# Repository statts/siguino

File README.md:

# Siguino

Low power board based on Arduino Pro Mini with in-built Sigfox network support

Siguino Eagle schematics, libraries and Arduino code created by Scott Tattersall

Further project info and manufactured boards for purchase at https://siguino.com

Detailed Getting Started Guide: https://siguino.com/step-by-step-guide/

3rd Party libraries / resources used:

Hardware:
- Many basic components (resistors, capacitors, etc) are from the SparkFun Eagle libraries
- LIS3DH accelerometer from SparkFun: https://github.com/sparkfun/SparkFun_LIS3DH_Arduino_Library
- Wisol Chip from hellogitty/WiSol (greatech.de) https://github.com/hellogitty/WiSOL

Software:
 (To install, go to url and "download zip", in Arduino IDE click Sketch->Include Library->Add zip and select downloaded zip file)
- LowPower library from RocketScream: https://github.com/rocketscream/Low-Power
- SparkFun LIS3DH library (https://github.com/sparkfun/SparkFun_LIS3DH_Arduino_Library)
- Arduino Sensors library (https://github.com/adafruit/Adafruit_Sensor)
- Arduino Bosch BME280 library (https://github.com/adafruit/Adafruit_BME280_Library)
- AltSoftSerial (https://github.com/PaulStoffregen/AltSoftSerial)

Enclosure:
- CAD (STL) files for sample enclosure that can be 3d printed as needed

# Sample projects
Along with the sigfox_sensors project that sends all sensor information here is another simple example project:

- Weather Station (arduino/weather_station)
Follow the same above software section to install the approriate libraries first, then download the weather station code.
The code can be flashed onto the Siguino via a standard FTDI breakout board (3.3v version only!), e.g. 
https://www.sparkfun.com/products/9873

The code: A simple weather station that sends avg temperature, light level, humidity and atmospheric pressure. If using Wia to process the data (see above getting started link), these can be easily graphed in Wia using a Wia Widget:
https://developers.wia.io/docs/add-a-widget

More information on integrating with Wia:
https://siguino.com/getting-started-with-siguino-and-wia-io/

Example:

")

# Eagle libraries
In eagle, set the directories for libraries to add the libary files included here if not already included, e.g.
$EAGLEDIR/lbr:{PROJECT-DIR}/Libraries/SparkFun-Eagle-Libraries-master:{PROJECT-DIR}/Libraries/WiSOL-master/Eagle_Library

Plus use the New Library -> execute script to add the components in script form from the scripts dir

# Hardware Revision History:

Rev 0.1: First version, trimmed board

Rev 0.2:
1) Add Reset Pin out as well as dtr for bootloading
2) Change C8 10uf format to standard 0603
3) Update routing to account for unsaved work
4) Re-write/tidy arduino sketch
5) Add de-coupling caps 10uf, 100nf to Accel chip VDD
6) Connect INT1 pin on Accel to D3

Rev 0.3:
1) Add Battery Holder
2) Add Reverse polarity Protection
3) Reposition Antenna

Rev 0.4:
1) Replace Temperature chip
2) Re-route temperature chip
3) Add registration hole for battery holder
4) Minor re-routing of vias under chips

Rev 0.5 / 1.0:
1) Added Magnetometer
2) Replaced temp chip with Temp & Pressure (Bosch BME 280)
3) Re-routing for manufacturing

Rev 1.1:
1) Improved Schematic (with thanks to Marnix Janse)
2) Improved Antenna trace (with thanks to Marnix Janse)

# Licence & Contact

Siguino Hardware and Software licenced under GPLv3, any questions or issues please contact scott@dock.ie

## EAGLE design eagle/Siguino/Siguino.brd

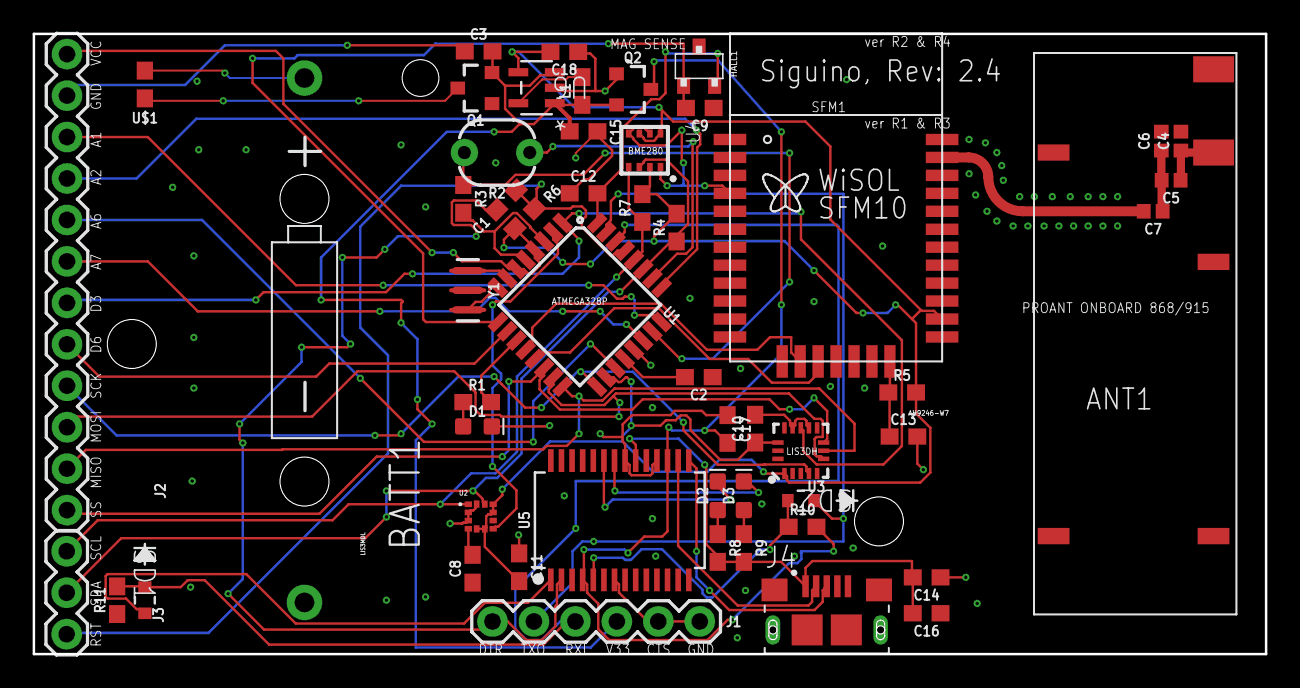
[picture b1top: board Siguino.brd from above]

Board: 2 copper layers, 75.5 x 38.0 mm, 53 parts (0 on the bottom side), 49 nets.

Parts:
ANT1: PRO-OB-471; ONBOARD_SMD_2400
BATT1: SPARKFUN-BATTERIES_CR2-BATTERY-HOLDERPTH; SPARKFUN-BATTERIES_BATTERYHOLDER-CR2
C1, C2, C3, C10, C11, C13, C14, C17: 0.1uF; 0603
C4: 0.6pF; 0402
C5: 2.2pF; 0402
C6: 0.7pF; 0402
C7: 0 OHM; 0402
C8: 100nF; 0603
C9: 10nF; 0603
C12: 100pF; 0603
C15, C16, C18: 10uF; 0603
D1, D2: RED; LED-0603
D3: GREEN; LED-0603
HALL1: TR-J_AH9246-W7; TR-J_SC-59
J1: FTDI; 1X06
J2: 1X12
J3: 1X03
J4: 10118193-0001LF; FCI_10118193-0001LF
L1: 10uH; 0603
Q1, Q2: MOSFET P-CH 20V 5.3A SOT-23; SOT23-3
R1: 330; 0603
R2: PHOTOCELLPTH; PHOTOCELL
R3, R8, R9, R10, R11: 1k; 0603
R4, R6, R7: 10k; 0603
R5: 100k; 0603
SD1, SD2: SD0603
SFM1: WISOL_WSSFM10
U1: ATMEGA328P_TQFP; TQFP32-08
U2: LIS3MDLTR_LIS3MDLTR; LIS3MDLTR_LGA12R50P4X4_200X200X100
U3: SPARKFUN-SENSORS_LIS3DH; SPARKFUN-SENSORS_LGA-16-3X3
U4: BME280; BME280COMPONENTLIBRARY_BME280_LGA
U5: FT232RL; SSOP28DB
U6: MAX1724EZK33+T; 21-0113C
U$1: PPTC; 0603
Y1: 8MHz; RESONATOR-SMD-3.2X1.3

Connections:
3V3FTDI: C17.2, Q2.3, R10.2, U5.4, U5.17
5V: C14.2, C16.2, J4.1, R8.2, R9.2, U5.20
A1: J2.10, U1.24
A2: J2.9, U1.25
A6: J2.8, U1.19
A7: J2.7, U1.22
D6: J2.5, U1.10
D7: R1.2, U1.11
DTR: C1.1, J1.1, U5.2
GND: ANT1.GND, BATT1.GND, C2.1, C3.1, C4.2, C6.2, C8.1, C9.1, C10.2, C11.1, C12.1, C13.2, C14.1, C15.1, C16.1, C17.1, C18.1, D1.C, HALL1.3, J1.5, J1.6, J2.11, J4.5, J4.S1, J4.S2, J4.S3, J4.S4, J4.S5, J4.S6, Q1.1, Q2.1, R3.2, R11.1, SFM1.1, SFM1.2, SFM1.3, SFM1.4, SFM1.20, SFM1.22, SFM1.27, SFM1.28, SFM1.29, SFM1.31, U1.3, U1.5, U1.21, U2.2, U2.3, U2.12, U3.5, U3.10, U3.12, U4.P$1, U4.P$5, U4.P$7, U5.7, U5.11, U5.18, U5.21, U5.25, U5.26, U6.2, Y1.2
HALL_POWER: C9.2, HALL1.1, U1.9
HALL_SENSE: C12.2, HALL1.2, U1.32
INT1: J2.6, U1.1, U3.11
LIGHT_POWER: R2.1, U1.26
LIGHT_SENSE: R2.2, R3.1, U1.23
MAG_INT: U1.2, U2.7
MISO: J2.2, U1.16, U3.7
MOSI: J2.3, U1.15, U3.6
unnamed: C2.2, U1.20
unnamed: U1.8, Y1.3
unnamed: U1.7, Y1.1
unnamed: ANT1.RF_FEED, C4.1, C5.1
unnamed: C13.1, R5.1, SFM1.19
unnamed: SD1.2, U5.1
unnamed: C5.2, C6.1, C7.1
unnamed: C8.2, U2.4
unnamed: R10.1, SD2.2, U5.5
unnamed: D2.A, R8.1
unnamed: D3.A, R9.1
unnamed: D2.C, U5.23
unnamed: D3.C, U5.22
unnamed: J4.2, U5.16
unnamed: J4.3, U5.15
unnamed: L1.2, U6.5
unnamed: D1.A, R1.1
RESET: C1.2, J3.1, R6.1, U1.29
RXI: J1.3, R11.2, SD1.1, U1.30
SCK: J2.4, U1.17, U3.4
SCL: J3.3, R7.1, U1.28, U2.1, U4.P$4
SDA: J3.2, R4.1, U1.27, U2.11, U4.P$3
SIG_RX: SFM1.15, U1.13
SIG_TX: SFM1.14, U1.12
SS: J2.1, U1.14, U3.8
TXO: J1.2, SD2.1, U1.31
VBAT: BATT1.VBATT, U$1.1
VBAT2: C3.2, C15.2, J1.4, L1.1, Q1.2, Q2.2, U6.1, U6.3
VCC: C10.1, C11.2, C18.2, J2.12, R4.2, R5.2, R6.2, R7.2, SFM1.21, U1.4, U1.6, U1.18, U2.5, U2.6, U2.9, U2.10, U3.1, U3.14, U4.P$2, U4.P$6, U4.P$8, U6.4
VSAFE: Q1.3, U$1.2
WISOL_ANT: C7.2, SFM1.30

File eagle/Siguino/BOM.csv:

"Part";"Value";"Device";"Package";"Description";"DESCRIPTION";"DIGI-KEY_PART_NUMBER";"DIGI-KEY_PURCHASE_URL";"MF";"MP";"PACKAGE";"PROD_ID";"SF_ID";"VALUE";
"ANT1";"PROOB471";"PROANT_PRO-OB-471_ONBOARD";"PROANT_ONBOARD_SMD_868_915";"Proant OnBoard Antenna PRO-OB-471 for 868/915MHz comms (e.g. SigFox)";"";"";"";"";"";"";"";"";"";
"BATT1";"SPARKFUN-BATTERIES_CR2-BATTERY-HOLDERPTH";"SPARKFUN-BATTERIES_CR2-BATTERY-HOLDERPTH";"SPARKFUN-BATTERIES_BATTERYHOLDER-CR2";"CR2 Battery holder from MPD, see DigiKey product here:";"";"";"";"";"";"";"";"";"";
"C1";"0.1uF";"0.1UF-0603-25V-5%";"0603";"0.1µF ceramic capacitors";"";"";"";"";"";"";"CAP-08604";"";"0.1uF";
"C2";"0.1uF";"0.1UF-0603-25V-5%";"0603";"0.1µF ceramic capacitors";"";"";"";"";"";"";"CAP-08604";"";"0.1uF";
"C3";"0.1uF";"0.1UF-0603-25V-5%";"0603";"0.1µF ceramic capacitors";"";"";"";"";"";"";"CAP-08604";"";"0.1uF";
"C4";"0.6pF";"0.8PF-0402-50V-0.1PF";"0402";"0.8pF ceramic capacitors";"";"";"";"";"";"";"CAP-13456";"";"0.8pF";
"C5";"2.2pF";"0.8PF-0402-50V-0.1PF";"0402";"0.8pF ceramic capacitors";"";"";"";"";"";"";"CAP-13456";"";"0.8pF";
"C6";"0.7pF";"0.8PF-0402-50V-0.1PF";"0402";"0.8pF ceramic capacitors";"";"";"";"";"";"";"CAP-13456";"";"0.8pF";
"C7";" 0 OHM";"RESISTOR0402";"0402";"Generic Resistor Package";"";"";"";"";"";"";" ";"";" ";
"C8";"100nF";"0.1UF-0603-25V-5%";"0603";"0.1µF ceramic capacitors";"";"";"";"";"";"";"CAP-08604";"";"0.1uF";
"C9";"10nF";"10NF-0603-50V-10%";"0603";"0.01uF/10nF/10,000pF ceramic capacitors";"";"";"";"";"";"";"CAP-00867";"";"10nF";
"C10";"0.1uF";"0.1UF-0603-25V-(+80/-20%)";"0603";"0.1µF ceramic capacitors";"";"";"";"";"";"";"CAP-00810";"";"0.1uF";
"C11";"0.1uF";"0.1UF-0603-25V-5%";"0603";"0.1µF ceramic capacitors";"";"";"";"";"";"";"CAP-08604";"";"0.1uF";
"C12";"100pF";"100PF-0603-50V-5%";"0603";"100pF/0.1nF ceramic capacitors";"";"";"";"";"";"";"CAP-07883";"";"100pF";
"C13";"0.1uF";"0.1UF-0603-25V-(+80/-20%)";"0603";"0.1µF ceramic capacitors";"";"";"";"";"";"";"CAP-00810";"";"0.1uF";
"C15";"10uF";"10UF-0603-6.3V-20%";"0603";"10.0µF ceramic capacitors";"";"";"";"";"";"";"CAP-11015";"";"10uF";
"D1";"RED";"LED-RED0603";"LED-0603";"Red SMD LED";"";"";"";"";"";"";"DIO-00819";"";"RED";
"HALL1";"TR-J_AH9246-W7";"TR-J_AH9246-W7";"TR-J_SC-59";"Hall effect switch, surface mount, part number AH9246-W-7";"";"";"";"";"";"";"";"";"";
"J1";"FTDI Basic";"6_PIN_SERIAL_TARGET";"1X06";"6-pin header connection for use with the "FTDI BASIC" pinout - TARGET SIDE.";"";"";"";"";"";"";"";"";"";
"J2";"";"CONN_12";"1X12";"Multi connection point. Often used as Generic Header-pin footprint for 0.1 inch spaced/style header connections";"";"";"";"";"";"";"";"";"";
"J3";"";"CONN_03";"1X03";"Multi connection point. Often used as Generic Header-pin footprint for 0.1 inch spaced/style header connections";"";"";"";"";"";"";"";"";"";
"Q1";"MOSFET P-CH 20V 5.3A SOT-23";"MOSFET_PCHSI2323DDS";"SOT23-3";"P-channel MOSFETs";"";"";"";"";"";"";"SI2323DDS-T1-GE3";"";"MOSFET P-CH 20V 5.3A SOT-23";
"R1";"330";"330OHM-0603-1/10W-1%";"0603";"330Ω resistor";"";"";"";"";"";"";"RES-00818";"";"330";
"R2";"PHOTOCELLPTH";"PHOTOCELLPTH";"PHOTOCELL";"Photocell (Photodetector, Photo Resistor, CdS)";"";"";"";"";"";"";"COMP-09129";"SEN-09088";"";
"R3";"1k";"1KOHM-0603-1/10W-1%";"0603";"1kΩ resistor";"";"";"";"";"";"";"RES-07856";"";"1k";
"R4";"10k";"10KOHM-0603-1/10W-1%";"0603";"10kΩ resistor";"";"";"";"";"";"";"RES-00824";"";"10k";
"R5";"100k";"100KOHM-0603-1/10W-1%";"0603";"100kΩ resistor";"";"";"";"";"";"";"RES-07828";"";"100k";
"R6";"10k";"10KOHM-0603-1/10W-1%";"0603";"10kΩ resistor";"";"";"";"";"";"";"RES-00824";"";"10k";
"R7";"10k";"10KOHM-0603-1/10W-1%";"0603";"10kΩ resistor";"";"";"";"";"";"";"RES-00824";"";"10k";
"SFM1";"";"WISOL_WSSFM10HANDSOLDER";"WISOL_WSSFM10";"WiSOL WSSFM10 Sigfox Module with PCB Footprint to enable handsolder";"";"";"";"";"";"";"";"";"";
"U1";"ATMEGA328P_TQFP";"ATMEGA328P_TQFP";"TQFP32-08";"Popular 328P in QFP";"";"";"";"";"";"";"IC-09069";"";"ATMEGA328P_TQFP";
"U2";"LIS3MDLTR_LIS3MDLTR";"LIS3MDLTR_LIS3MDLTR";"LIS3MDLTR_LGA12R50P4X4_200X200X100";"LIS3MDL Series 3 Axis ±2/±8/±12/±16 g 3.6V High Performance Magnetometer LGA-12";"SENSOR MAGMTR I2C/SPI 12LGA";"497-13892-1-ND";"https://www.digikey.co.uk/product-detail/en/stmicroelectroni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";"STMicroelectronics";"LIS3MDLTR";"VFLGA-12 STMicroelectronics";"";"";"";
"U3";"SPARKFUN-SENSORS_LIS3DH";"SPARKFUN-SENSORS_LIS3DH";"SPARKFUN-SENSORS_LGA-16-3X3";"ST Microelectronics LIS3DH 3-Axis +/-2/4/8/16g SPI/I2C Accelerometer";"";"";"";"";"";"";"IC-13419";"N/A";"";
"U4";"BME280";"BME280COMPONENTLIBRARY_BME280";"BME280COMPONENTLIBRARY_BME280_LGA";"";"";"";"";"";"";"";"IC-13090";"";"BME280";
"Y1";"8MHz";"RESONATOR-8MHZSMD_3.2X1.3";"RESONATOR-SMD-3.2X1.3";"8MHz Resonator";"";"";"";"";"";"";"XTAL-08895";"";"8MHz";

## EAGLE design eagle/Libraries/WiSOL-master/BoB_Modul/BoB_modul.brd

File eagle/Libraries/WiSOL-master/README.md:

# WiSOL
Eagle Library and demo source codes for WiSOL Sigfox Modules

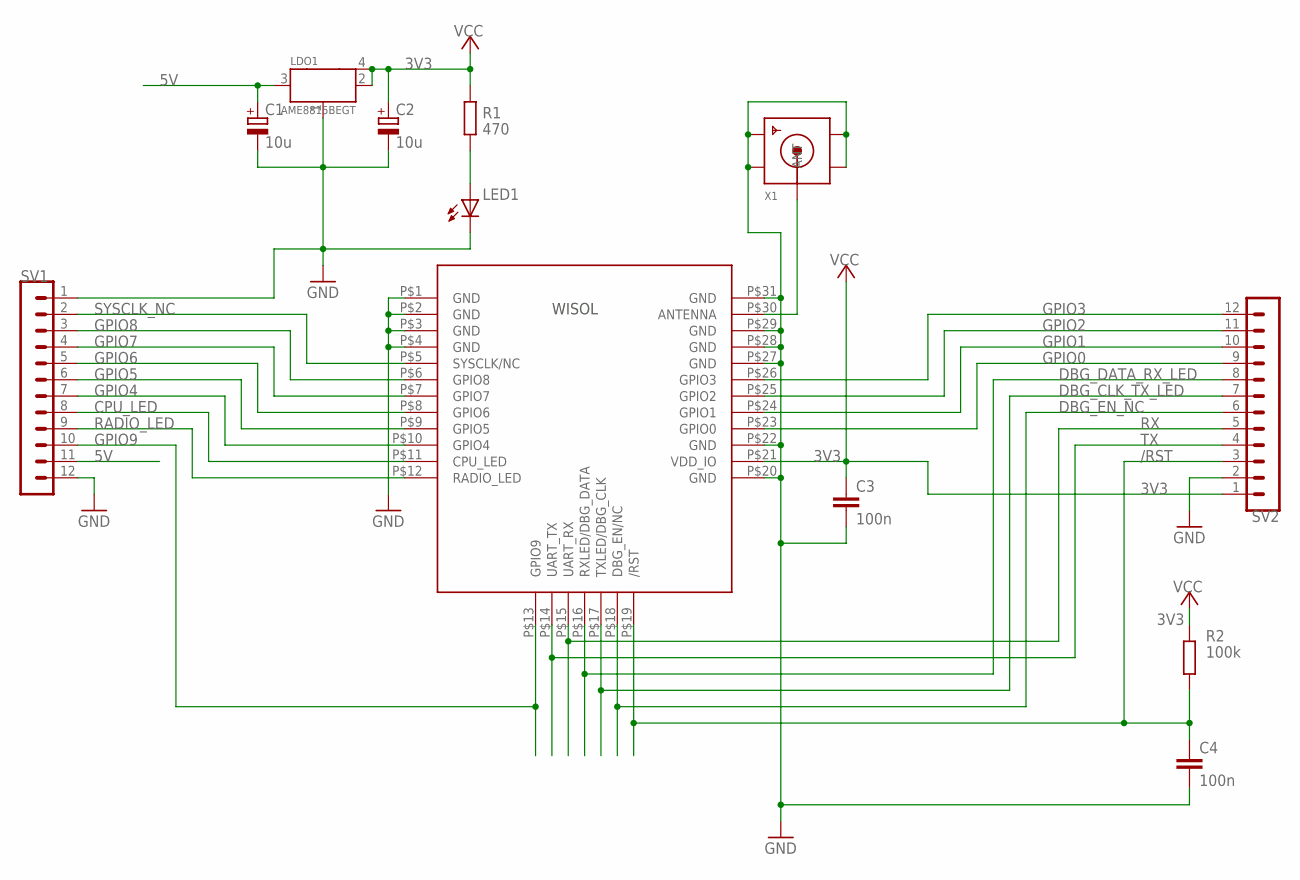
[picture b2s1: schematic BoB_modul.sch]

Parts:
C1, C2: 10u; A/3216-18R
C3, C4: 100n; C0603K
LDO1: AME8815BEGT; SOT223
LED1: LEDCHIPLED_0603; CHIPLED_0603
R1: 470; R0603
R2: 100k; R0603
SV1, SV2: MA12-1
WSSFM10: SFM10; WSSFM10
X1: SMACONNECTOR_EDGE_UFL; SMA_EDGELAUNCH_UFL

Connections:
3V3: C2.+, C3.1, LDO1.2, LDO1.4, R1.2, R2.2, SV2.1, WSSFM10.P$21 (VDD_IO)
5V: C1.+, LDO1.3, SV1.11
/RST: C4.1, R2.1, SV2.3, WSSFM10.P$19 (/RST)
CPU_LED: SV1.8, WSSFM10.P$11 (CPU_LED)
DBG_CLK_TX_LED: SV2.7, WSSFM10.P$17 (TXLED/DBG_CLK)
DBG_DATA_RX_LED: SV2.8, WSSFM10.P$16 (RXLED/DBG_DATA)
DBG_EN_NC: SV2.6, WSSFM10.P$18 (DBG_EN/NC)
GND: C1.-, C2.-, C3.2, C4.2, LDO1.1, LED1.C, SV1.1, SV1.12, SV2.2, WSSFM10.P$1 (GND), WSSFM10.P$2 (GND), WSSFM10.P$3 (GND), WSSFM10.P$4 (GND), WSSFM10.P$20 (GND), WSSFM10.P$22 (GND), WSSFM10.P$27 (GND), WSSFM10.P$28 (GND), WSSFM10.P$29 (GND), WSSFM10.P$31 (GND), X1.GND@1 (GND1), X1.GND@2 (GND2), X1.GND@3 (GND3), X1.GND@4 (GND4)
GPIO0: SV2.9, WSSFM10.P$23 (GPIO0)
GPIO1: SV2.10, WSSFM10.P$24 (GPIO1)
GPIO2: SV2.11, WSSFM10.P$25 (GPIO2)
GPIO3: SV2.12, WSSFM10.P$26 (GPIO3)
GPIO4: SV1.7, WSSFM10.P$10 (GPIO4)
GPIO5: SV1.6, WSSFM10.P$9 (GPIO5)
GPIO6: SV1.5, WSSFM10.P$8 (GPIO6)
GPIO7: SV1.4, WSSFM10.P$7 (GPIO7)
GPIO8: SV1.3, WSSFM10.P$6 (GPIO8)
GPIO9: SV1.10, WSSFM10.P$13 (GPIO9)
unnamed: LED1.A, R1.1
unnamed: WSSFM10.P$30 (ANTENNA), X1.P (ANT)
RADIO_LED: SV1.9, WSSFM10.P$12 (RADIO_LED)
RX: SV2.5, WSSFM10.P$15 (UART_RX)
SYSCLK_NC: SV1.2, WSSFM10.P$5 (SYSCLK/NC)
TX: SV2.4, WSSFM10.P$14 (UART_TX)

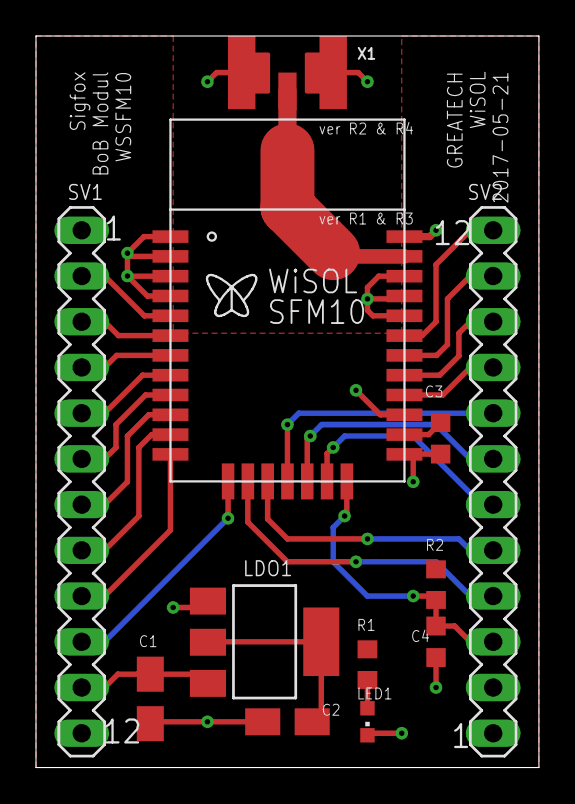
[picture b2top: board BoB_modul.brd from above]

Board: 2 copper layers, 27.9 x 40.6 mm, 12 parts (0 on the bottom side), 24 nets.

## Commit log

2017-12-07 Update readme with links
2017-12-07 Update readme markdown
2018-05-29 Updated with latest 0.5 and 1.0 changes
2018-07-19 Updated library links and getting started guide
2018-07-22 Fixed bug with total counters being re-zeroed in loop
2018-07-31 Extended send period to 15 mins
2018-08-29 Added additional example project for weather station
2018-08-29 Updated readme with reference to new project
2018-08-30 Updated image for temperature chart in samle project
2018-08-30 Updated position of chart image
2018-08-30 Fixed positioning
2018-09-14 Updated with fix for US FCC rules and WISOL SFM10R2 chip
2018-09-14 Updated weather station to send every 15 mins
2018-11-02 Updated readme with Getting Started Guide link
2018-11-08 Cleaned schematic & changed antenna path on Board
2018-11-21 Updated board and schematic with ERC and DRC check approvals
2018-11-21 Added cad files for 3d printing enclosure
2018-11-21 Fixed enclosure images
2018-11-21 Fixed enclosure images sizes
2018-12-10 Updated BOM
2018-12-15 Added new components and re-organised board, unrouted
2018-12-16 Re-routed board, unfinished
2018-12-20 Finalised v2.0 and re-routed, gerbers created
2018-12-20 Dir tidy & added cam processor file used for v2 gerbers
2019-02-28 Fixed bit packing issue up to 64bits
2019-03-06 Fixed hatching issue on antenna pads, fixed FTDI problem
2019-03-12 Minor updates
2019-03-12 Moved components and resized board to fit box
2019-03-27 Fixed issue with hatching on antenna pads causing RF issues
2019-03-27 Repo cleanup and added gitignore
2019-05-22 Added PPTC over current protection
2019-05-23 Version text changed
2020-01-28 Various updates
2021-02-13 KiCad Siguino Version
    Updated .gitignore for specific kicad files and added a folder with schematic and pcb converted to KiCad

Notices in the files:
parts and their libraries:
SparkFun-Capacitors: Licensing: Creative Commons ShareAlike 4.0 International - https://creativecommons.org/licenses/by-sa/4.0
